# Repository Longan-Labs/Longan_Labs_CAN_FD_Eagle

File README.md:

# Longan_Labs_CAN_FD_Eagle
Eagle file for CAN-FD Shield

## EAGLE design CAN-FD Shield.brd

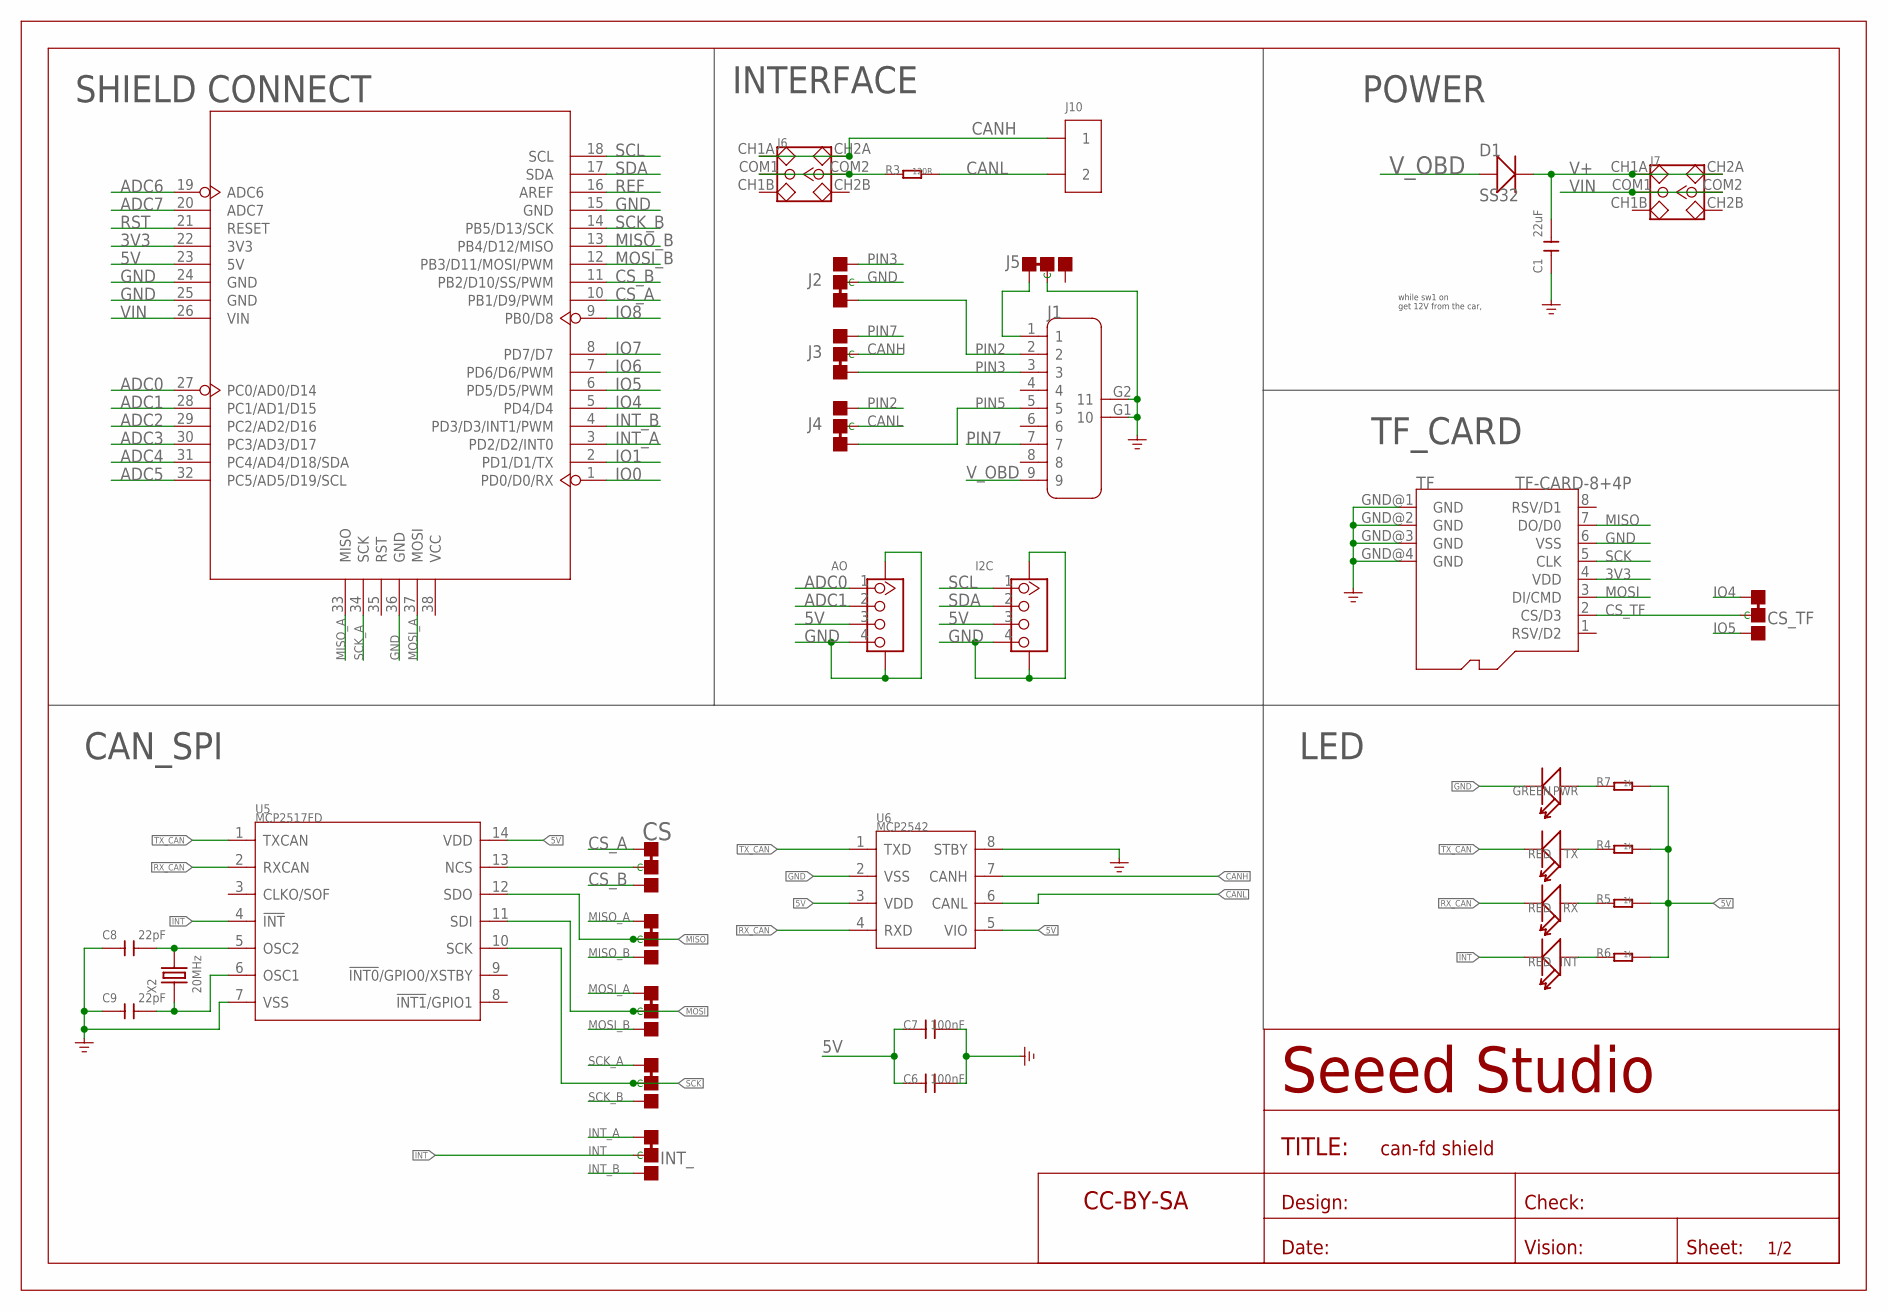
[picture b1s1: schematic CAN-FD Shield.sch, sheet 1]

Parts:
AO: GROVE-CONNECTOR-SMD'90D'; HW4-SMD-2.0-90D
C1: 22uF; C1206
C6, C7: 100nF; 0603
C8, C9: 22pF; C0603
CS: JUMPER-3P-SHORT; 3P-SMD-SHORT
CS_TF: JUMPER-3P-SHORT; 3P-SMD-SHORT
D1: SS32; D2010
I2C: GROVE-CONNECTOR-SMD'90D'; HW4-SMD-2.0-90D
INT: RED; LED-0603
INT_: JUMPER-3P-SHORT; 3P-SMD-SHORT
J1: DB9'MEAL'; DB9-MEAL
J2, J3, J4, J5: JUMPER-3P-SHORT; 3P-SMD-SHORT
J6, J7: SWITCH-2CH-6P; 6P-2CH-2.54-7.6X3.0
J10: SCREW-TERMINAL-2P'5.08'; H2-5.0-10.5X8.0MM
MISO: JUMPER-3P-SHORT; 3P-SMD-SHORT
MOSI: JUMPER-3P-SHORT; 3P-SMD-SHORT
PWR: GREEN; LED-0603
R3: 120R; 0603
R4, R5, R6, R7: 1k; 0603
RX: RED; LED-0603
SCK: JUMPER-3P-SHORT; 3P-SMD-SHORT
TF: TF-CARD-8+4P; TF-8+4P-1.1-13.5X15MM
TX: RED; LED-0603
U4: ARDUINO-38P'WITH/-SILK'; ARDUINO-38P-WITH/-SILK-500519002
U5: MCP2517FD; SOIC14-1.27-8.6X3.9MM
U6: MCP2542; SOIC8-1.27-5X4MM
U$5: SEEEDSTUDIO-OPEN-SCH-FRAME; SEEEDSTUDIO-PCB-FRAME
X2: 20MHz; HC49US

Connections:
3V3: TF.4 (VDD), U4.22 (3V3)
5V: AO.3, C6.1, C7.1, I2C.3, R4.2, R5.2, R6.2, R7.2, U4.23 (5V), U5.14 (VDD), U6.3 (VDD), U6.5 (VIO)
ADC0: AO.1, U4.27 (PC0/AD0/D14)
ADC1: AO.2, U4.28 (PC1/AD1/D15)
ADC2: U4.29 (PC2/AD2/D16)
ADC3: U4.30 (PC3/AD3/D17)
ADC4: U4.31 (PC4/AD4/D18/SDA)
ADC5: U4.32 (PC5/AD5/D19/SCL)
ADC6: U4.19 (ADC6)
ADC7: U4.20 (ADC7)
CANH: J3.MM (C), J6.CH1A, J6.CH2A, J10.1, U6.7 (CANH)
CANL: J4.MM (C), J10.2, R3.2, U6.6 (CANL)
CS_A: CS.11 (L), U4.10 (PB1/D9/PWM)
CS_B: CS.00 (R), U4.11 (PB2/D10/SS/PWM)
CS_TF: CS_TF.MM (C), TF.2 (CS/D3)
GND: AO.4, AO.SS1, AO.SS2, C1.1, C6.2, C7.2, C8.1, C9.1, I2C.4, I2C.SS1, I2C.SS2, J1.G1 (10), J1.G2 (11), J2.MM (C), J5.MM (C), PWR.-, TF.6 (VSS), TF.GND@1 (GND), TF.GND@2 (GND), TF.GND@3 (GND), TF.GND@4 (GND), U4.15 (GND), U4.24 (GND), U4.25 (GND), U4.36 (GND), U5.7 (VSS), U6.2 (VSS), U6.8 (STBY)
INT: INT.-, INT_.MM (C), U5.4 (!INT)
INT_A: INT_.11 (L), U4.3 (PD2/D2/INT0)
INT_B: INT_.00 (R), U4.4 (PD3/D3/INT1/PWM)
IO0: U4.1 (PD0/D0/RX)
IO1: U4.2 (PD1/D1/TX)
IO4: CS_TF.11 (L), U4.5 (PD4/D4)
IO5: CS_TF.00 (R), U4.6 (PD5/D5/PWM)
IO6: U4.7 (PD6/D6/PWM)
IO7: U4.8 (PD7/D7)
IO8: U4.9 (PB0/D8)
MISO: MISO.MM (C), TF.7 (DO/D0), U5.12 (SDO)
MISO_A: MISO.11 (L), U4.33 (MISO)
MISO_B: MISO.00 (R), U4.13 (PB4/D12/MISO)
MOSI: MOSI.MM (C), TF.3 (DI/CMD), U5.11 (SDI)
MOSI_A: MOSI.11 (L), U4.37 (MOSI)
MOSI_B: MOSI.00 (R), U4.12 (PB3/D11/MOSI/PWM)
unnamed: PWR.+, R7.1
unnamed: R4.1, TX.+
unnamed: J6.COM1, J6.COM2, R3.1
unnamed: J1.1, J5.11 (L)
unnamed: C8.2, U5.5 (OSC2), X2.2
unnamed: CS.MM (C), U5.13 (NCS)
unnamed: R5.1, RX.+
unnamed: C9.2, U5.6 (OSC1), X2.1
unnamed: INT.+, R6.1
PIN2: J1.2, J2.11 (L), J4.00 (R)
PIN3: J1.3, J2.00 (R), J3.11 (L)
PIN5: J1.5, J4.11 (L)
PIN7: J1.7, J3.00 (R)
REF: U4.16 (AREF)
RST: U4.21 (RESET)
RX_CAN: RX.-, U5.2 (RXCAN), U6.4 (RXD)
SCK: SCK.MM (C), TF.5 (CLK), U5.10 (SCK)
SCK_A: SCK.11 (L), U4.34 (SCK)
SCK_B: SCK.00 (R), U4.14 (PB5/D13/SCK)
SCL: I2C.1, U4.18 (SCL)
SDA: I2C.2, U4.17 (SDA)
TX_CAN: TX.-, U5.1 (TXCAN), U6.1 (TXD)
V+: C1.2, D1.-, J7.CH1A, J7.CH2A
VIN: J7.COM1, J7.COM2, U4.26 (VIN)
V_OBD: D1.+, J1.9

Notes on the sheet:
CAN_SPI
SHIELD CONNECT
INTERFACE
POWER
get 12V from the car,
while sw1 on
TF_CARD
LED

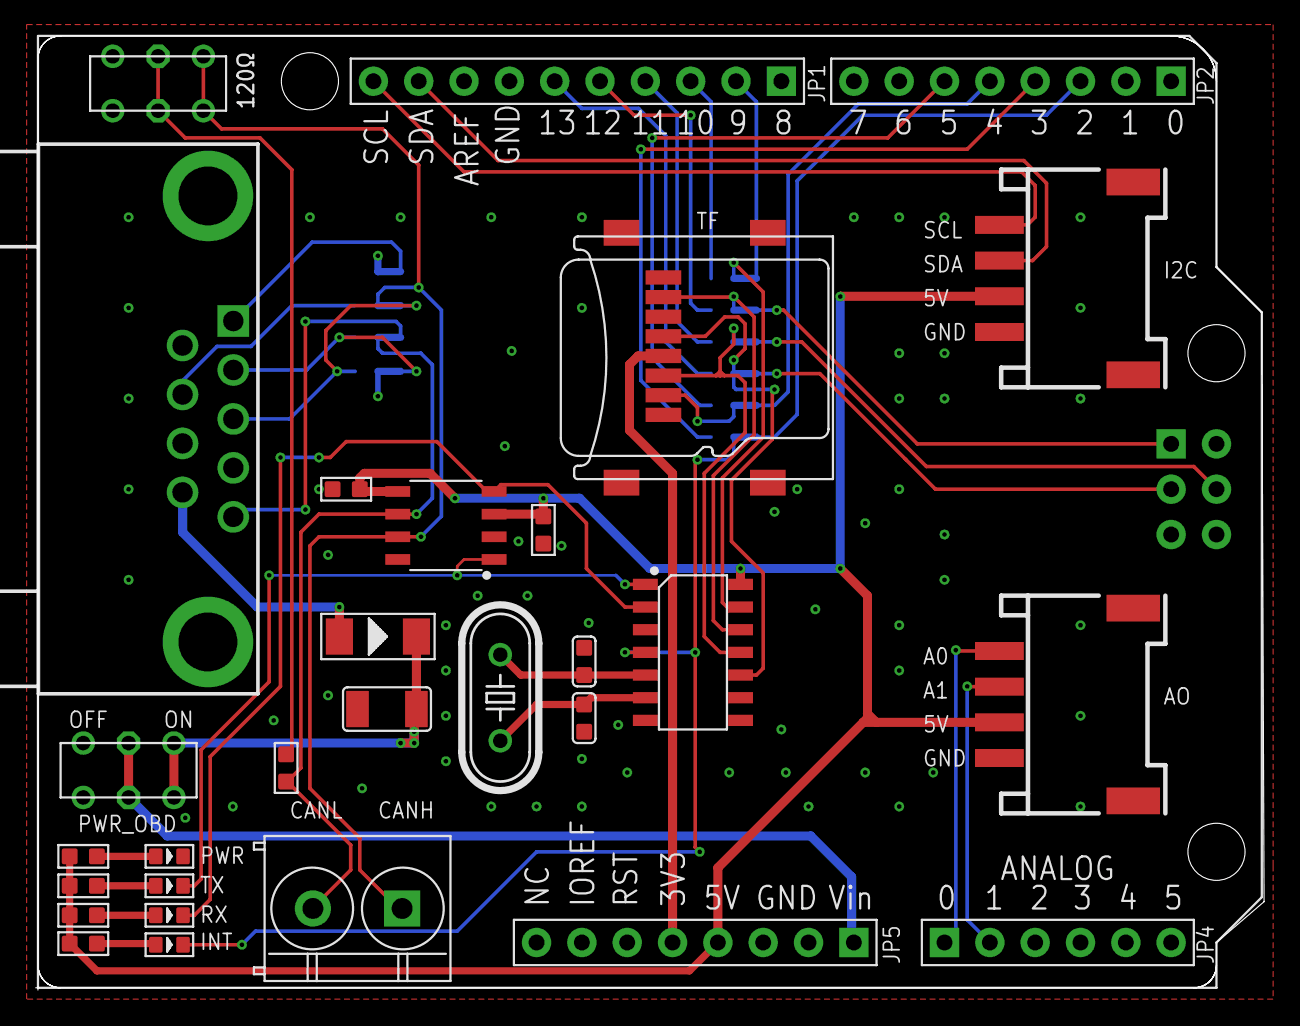
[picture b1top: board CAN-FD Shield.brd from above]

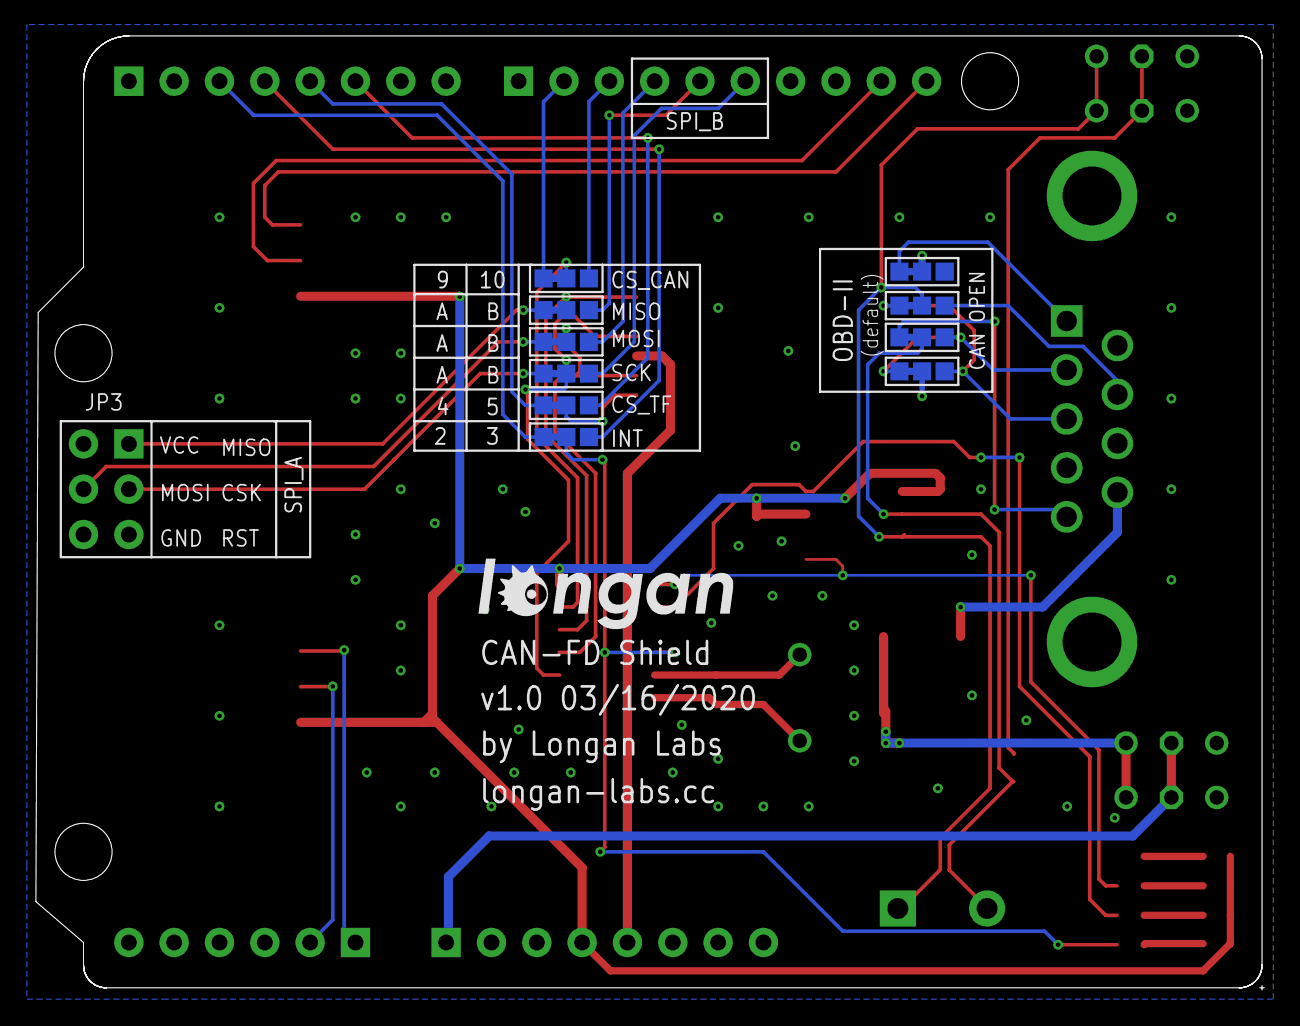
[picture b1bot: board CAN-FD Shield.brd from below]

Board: 2 copper layers, 68.8 x 53.5 mm, 38 parts (11 on the bottom side), 44 nets.

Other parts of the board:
U$1: LONGAN-SILK-SMALLER

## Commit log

2020-04-13 first push

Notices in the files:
parts and their libraries:
moudle-new: This work is licensed under the Creative Commons Attribution 4.0 International License.
To view a copy of this license,visit:
http://creativecommons.org/licenses/by-sa/4.0
moudle-new: CC-BY-SA
